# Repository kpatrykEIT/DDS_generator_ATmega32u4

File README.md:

# DDS_generator_ATmega32u4

Periodic waveform generator project based on Direct Digital Synthesis (DDS). The system utilizes an ATmega32u4 microcontroller and a TLC7524C DAC. Developed low-level firmware in C using direct register manipulation. Designed the PCB in KiCad.

<table>
  <tr>
    <td></td>
    <td></td>
  </tr>
  <tr>
    <td></td>
  <td></td>
  </tr>
</table>

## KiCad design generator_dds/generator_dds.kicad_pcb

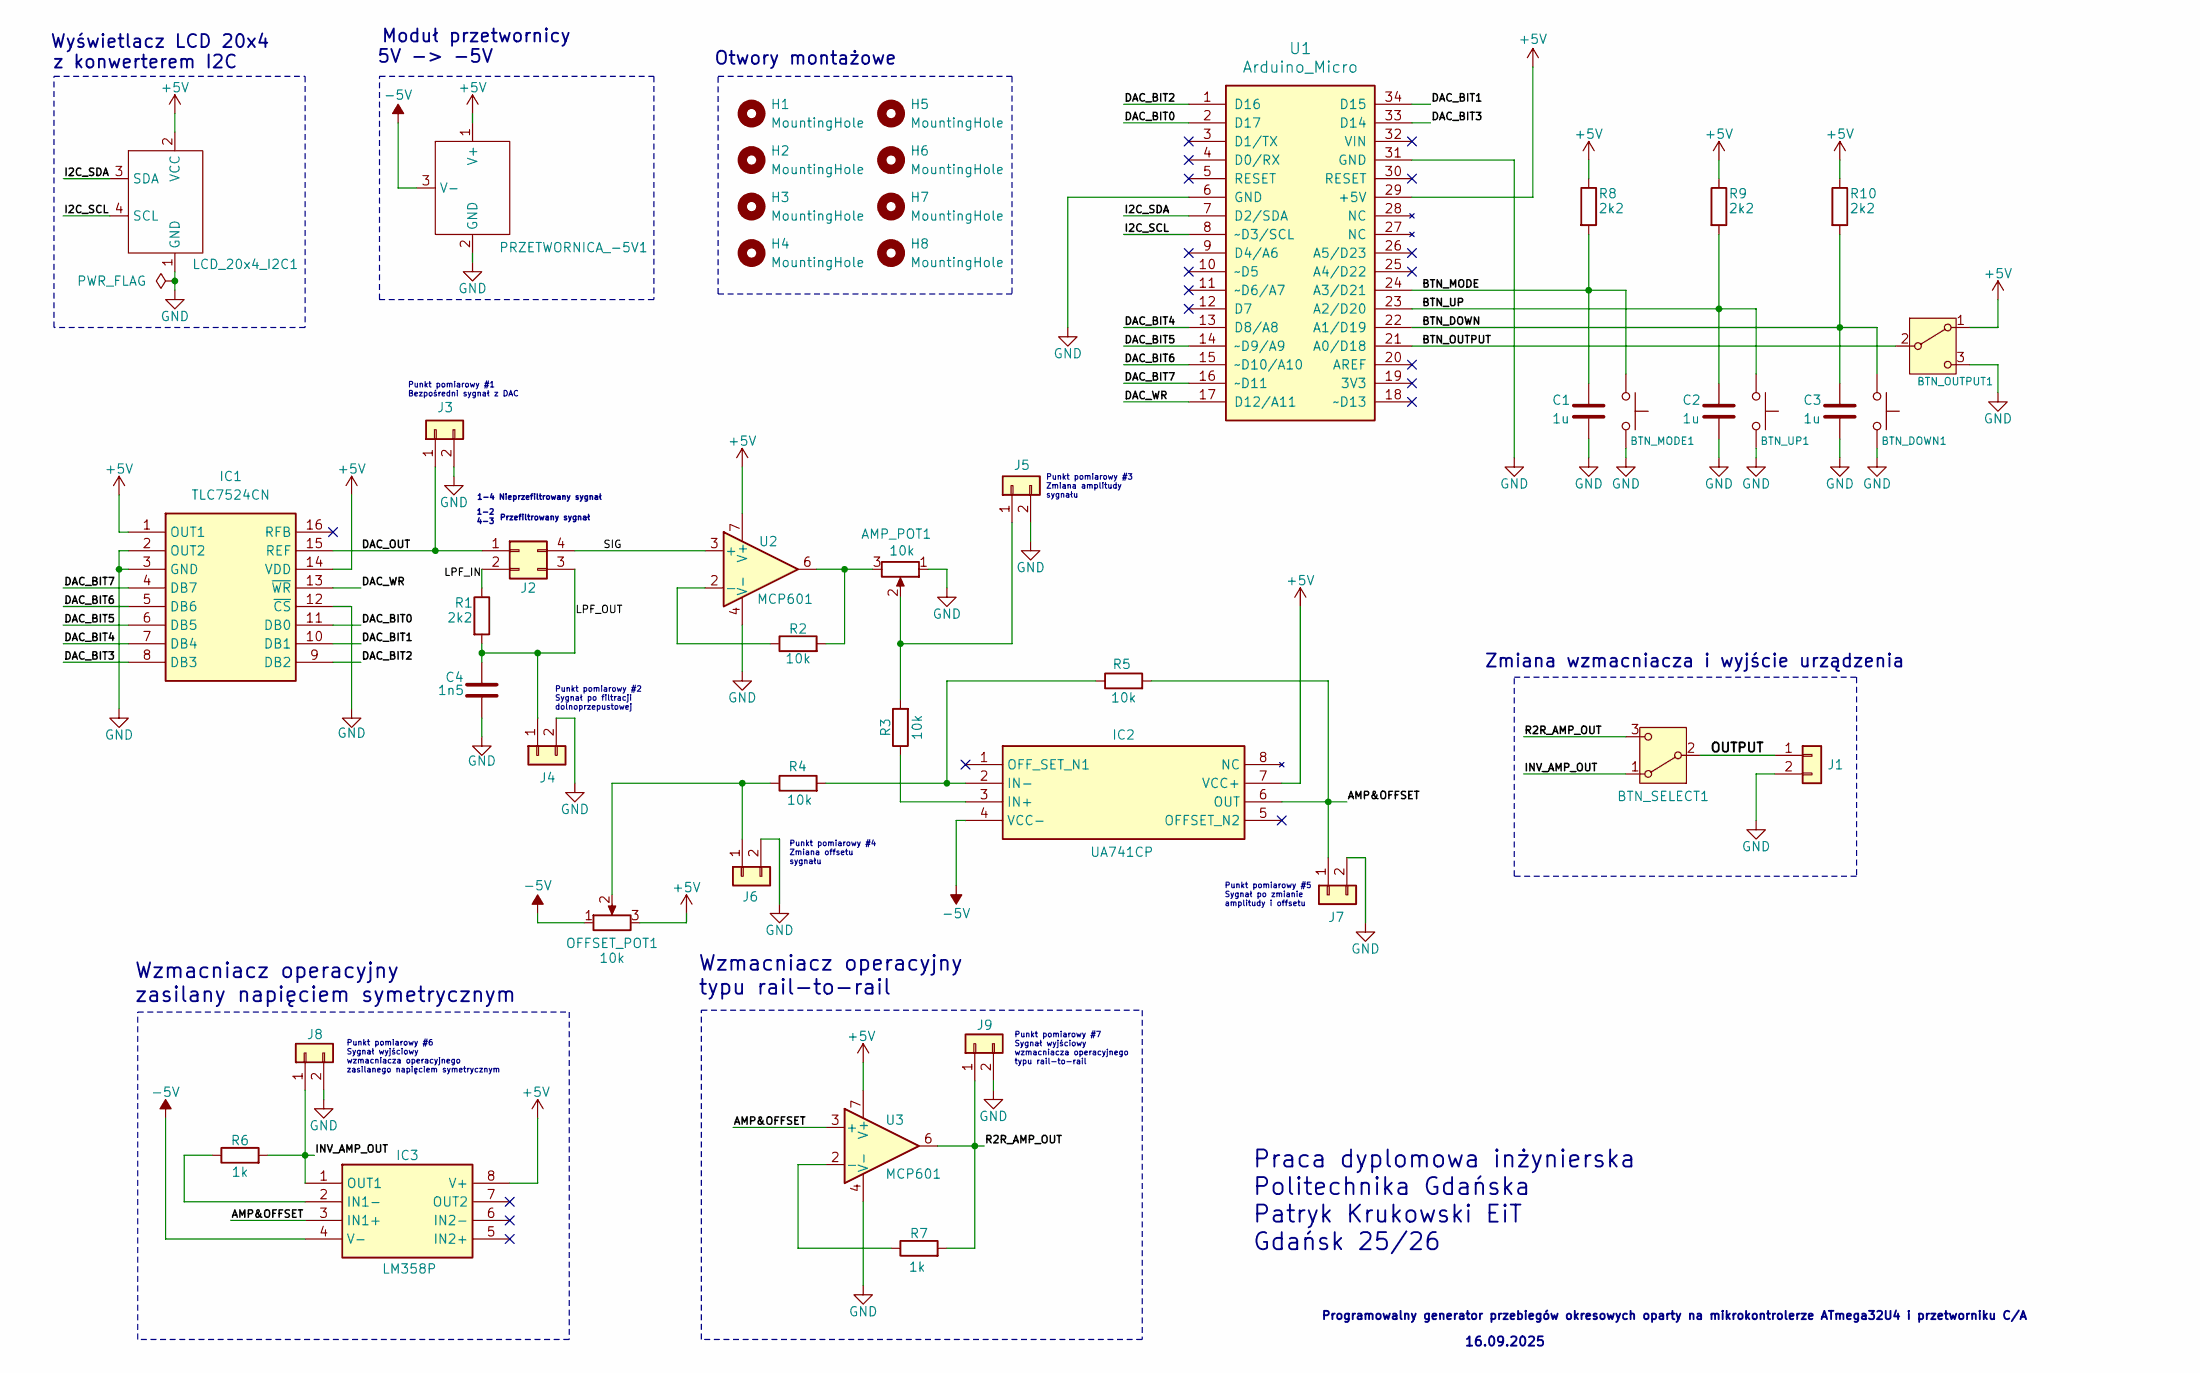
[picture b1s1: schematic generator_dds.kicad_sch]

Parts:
AMP_POT1: 10k; Potentiometer_Runtron_RM-065_Vertical
BTN_DOWN1: SW_Push; PRZYCISK_2P_5mm
BTN_MODE1: SW_Push; PRZYCISK_2P_5mm
BTN_OUTPUT1: SW_SPDT; PRZELACZNIK_SPDT_5mm
BTN_SELECT1: SW_SPDT; PRZELACZNIK_SPDT_5mm
BTN_UP1: SW_Push; PRZYCISK_2P_5mm
C1, C2, C3: 1u; C_Disc_D3.4mm_W2.1mm_P2.50mm
C4: 1n5; C_Disc_D4.3mm_W1.9mm_P5.00mm
H1, H2, H3, H4, H5, H6, H7, H8: MountingHole; MountingHole_4.3mm_M4_DIN965_Pad
IC1: TLC7524CN; DIP794W53P254L1930H508Q16N; Mouser Part Number 595-TLC7524CN
IC2: UA741CP; DIP794W53P254L959H508Q8N; Mouser Part Number 595-UA741CP
IC3: LM358P; DIP794W53P254L959H508Q8N; Mouser Part Number 595-LM358P
J1, J3, J4, J5, J6, J7, J8, J9: Conn_01x02; PinHeader_1x02_P2.54mm_Vertical
J2: Conn_02x02_Counter_Clockwise; PinHeader_2x02_P2.00mm_Vertical
LCD_20x4_I2C1: LCD_20x4_I2C_TESTfp
OFFSET_POT1: 10k; Potentiometer_Runtron_RM-065_Vertical
PRZETWORNICA_-5V1: PRZETWORNICA_5V
R1, R8, R9, R10: 2k2; R_Axial_DIN0207_L6.3mm_D2.5mm_P7.62mm_Horizontal
R2, R3, R4, R5: 10k; R_Axial_DIN0207_L6.3mm_D2.5mm_P7.62mm_Horizontal
R6, R7: 1k; R_Axial_DIN0207_L6.3mm_D2.5mm_P7.62mm_Horizontal
U1: Arduino_Micro
U2, U3: MCP601; DIP-8_W7.62mm

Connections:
+5V: BTN_OUTPUT1.1 (A), IC1.1 (OUT1), IC1.14 (VDD), IC2.7 (VCC+), IC3.8 (V+), LCD_20x4_I2C1.2 (VCC), OFFSET_POT1.3, PRZETWORNICA_-5V1.1 (V+), R8.1, R9.1, R10.1, U1.29 (+5V), U2.7 (V+), U3.7 (V+); also elsewhere on the board
-5V: IC2.4 (VCC-), IC3.4 (V-), OFFSET_POT1.1, PRZETWORNICA_-5V1.3 (V-); also elsewhere on the board
/AMP&OFFSET: IC2.6 (OUT), IC3.3 (IN1+), J7.1, R5.2, U3.3 (+)
/BTN_DOWN: BTN_DOWN1.1, C3.1, R10.2, U1.22 (A1/D19)
/BTN_MODE: BTN_MODE1.1, C1.1, R8.2, U1.24 (A3/D21)
/BTN_OUTPUT: BTN_OUTPUT1.2 (B), U1.21 (A0/D18); also elsewhere on the board
/BTN_UP: BTN_UP1.1, C2.1, R9.2, U1.23 (A2/D20)
/DAC_BIT0: IC1.11 (DB0), U1.2 (D17)
/DAC_BIT1: IC1.10 (DB1), U1.34 (D15)
/DAC_BIT2: IC1.9 (DB2), U1.1 (D16)
/DAC_BIT3: IC1.8 (DB3), U1.33 (D14)
/DAC_BIT4: IC1.7 (DB4), U1.13 (D8/A8)
/DAC_BIT5: IC1.6 (DB5), U1.14 (~D9/A9)
/DAC_BIT6: IC1.5 (DB6), U1.15 (~D10/A10)
/DAC_BIT7: IC1.4 (DB7), U1.16 (~D11)
/DAC_OUT: IC1.15 (REF), J2.1, J3.1
/DAC_WR: IC1.13 (~WR), U1.17 (D12/A11)
/I2C_SCL: LCD_20x4_I2C1.4 (SCL), U1.8 (~D3/SCL)
/I2C_SDA: LCD_20x4_I2C1.3 (SDA), U1.7 (D2/SDA)
/INV_AMP_OUT: BTN_SELECT1.1 (A), IC3.1 (OUT1), J8.1, R6.2; also elsewhere on the board
/LPF_IN: J2.2, R1.1
/LPF_OUT: C4.1, J2.3, J4.1, R1.2
/OUTPUT: BTN_SELECT1.2 (B), J1.1; also elsewhere on the board
/R2R_AMP_OUT: BTN_SELECT1.3 (C), J9.1, R7.2, U3.6; also elsewhere on the board
/SIG: J2.4, U2.3 (+)
GND: AMP_POT1.1, BTN_DOWN1.2, BTN_MODE1.2, BTN_OUTPUT1.3 (C), BTN_UP1.2, C1.2, C2.2, C3.2, C4.2, IC1.2 (OUT2), IC1.3 (GND), IC1.12 (~CS), J1.2, J3.2, J4.2, J5.2, J6.2, J7.2, J8.2, J9.2, LCD_20x4_I2C1.1 (GND), PRZETWORNICA_-5V1.2 (GND), U1.6 (GND), U1.31 (GND), U2.4 (V-), U3.4 (V-); also elsewhere on the board
unnamed 26: AMP_POT1.3, R2.2, U2.6; also elsewhere on the board
unnamed: IC2.3 (IN+), R3.1
unnamed: IC2.2 (IN-), R4.2, R5.1
unnamed: IC3.2 (IN1-), R6.1
unnamed 30: AMP_POT1.2, J5.1, R3.2; also elsewhere on the board
unnamed 31: J6.1, OFFSET_POT1.2, R4.1; also elsewhere on the board
unnamed: R2.1, U2.2 (-)
unnamed: R7.1, U3.2 (-)

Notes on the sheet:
Przefiltrowany sygnał
1-4 Nieprzefiltrowany sygnał
Wyświetlacz LCD 20x4
Otwory montażowe
Wzmacniacz operacyjny typu rail-to-rail
5V -> -5V
Punkt pomiarowy #7 Sygnał wyjściowy wzmacniacza operacyjnego typu rail-to-rail
Punkt pomiarowy #1 Bezpośredni sygnał z DAC
1-2
Punkt pomiarowy #2 Sygnał po filtracji dolnoprzepustowej
Praca dyplomowa inżynierska Politechnika Gdańska Patryk Krukowski EiT Gdańsk 25/26
16.09.2025
z konwerterem I2C
Moduł przetwornicy
Punkt pomiarowy #5 Sygnał po zmianie amplitudy i offsetu
Punkt pomiarowy #3 Zmiana amplitudy sygnału
Punkt pomiarowy #4 Zmiana offsetu sygnału
4-3
Zmiana wzmacniacza i wyjście urządzenia
Programowalny generator przebiegów okresowych oparty na mikrokontrolerze ATmega32U4 i przetworniku C/A
Punkt pomiarowy #6 Sygnał wyjściowy wzmacniacza operacyjnego zasilanego napięciem symetrycznym
Wzmacniacz operacyjny zasilany napięciem symetrycznym

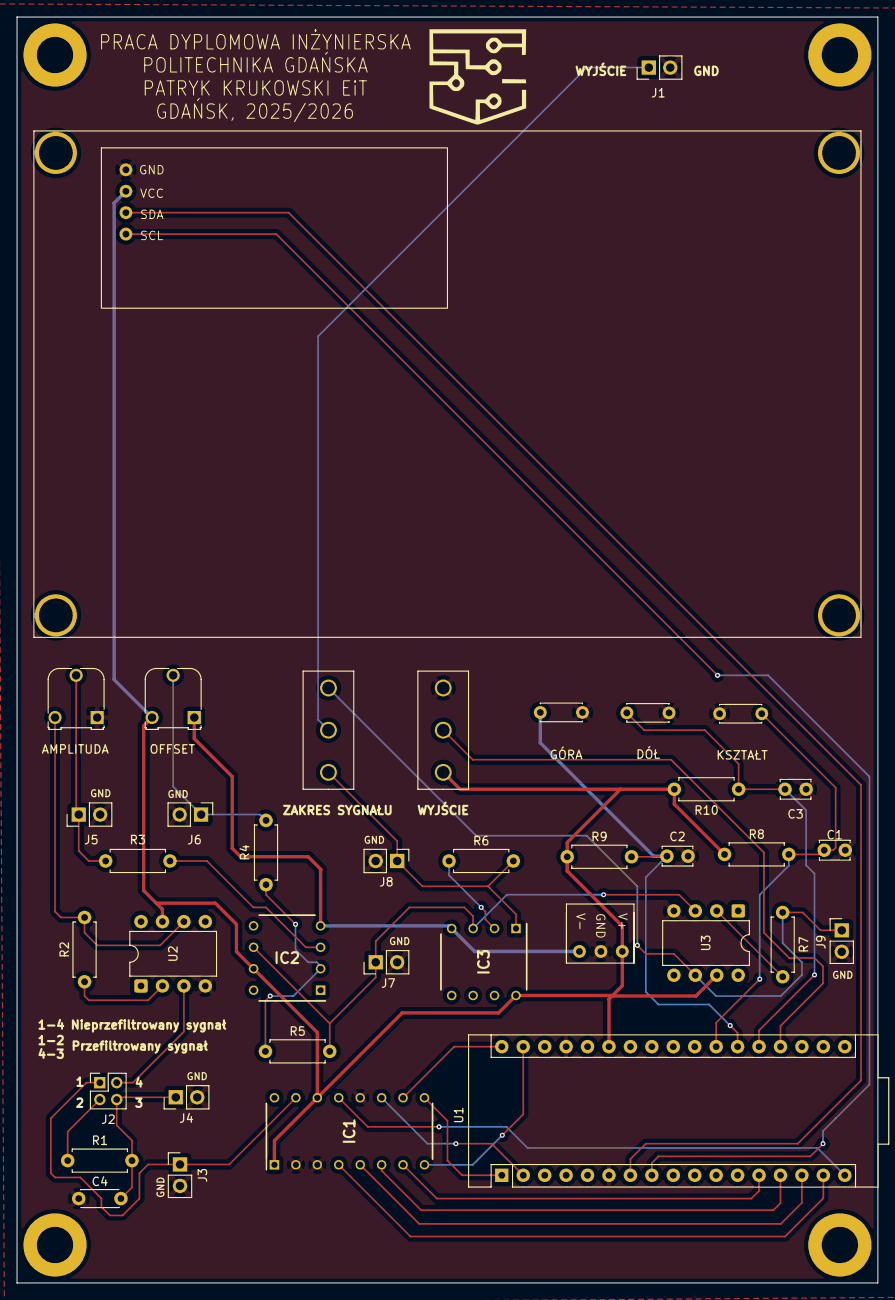
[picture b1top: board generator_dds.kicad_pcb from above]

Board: 4 copper layers, 102.0 x 150.0 mm, 46 parts (0 on the bottom side), 34 nets.

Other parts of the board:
AMPLITUDA: 10k; Potentiometer_Runtron_RM-065_Vertical
OFFSET: 10k; Potentiometer_Runtron_RM-065_Vertical
WYJŚCIE: SW_SPDT; PRZELACZNIK_SPDT_5mm
ZAKRES SYGNAŁU: SW_SPDT; PRZELACZNIK_SPDT_5mm

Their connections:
+5V: OFFSET.3, WYJŚCIE.1 (A); also elsewhere on the board
-5V: OFFSET.1; also elsewhere on the board
/BTN_OUTPUT: WYJŚCIE.2 (B); also elsewhere on the board
/INV_AMP_OUT: ZAKRES SYGNAŁU.1 (A); also elsewhere on the board
/OUTPUT: ZAKRES SYGNAŁU.2 (B); also elsewhere on the board
/R2R_AMP_OUT: ZAKRES SYGNAŁU.3 (C); also elsewhere on the board
GND: AMPLITUDA.1, WYJŚCIE.3 (C); also elsewhere on the board
unnamed 26: AMPLITUDA.3; also elsewhere on the board
unnamed 30: AMPLITUDA.2; also elsewhere on the board
unnamed 31: OFFSET.2; also elsewhere on the board

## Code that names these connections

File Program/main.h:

/*
 * File: main.h
 *
 * Created: 02.06.2025 17:09:30
 *  Author: Patryk Krukowski
 */ 


#ifndef MAIN_H_
#define MAIN_H_

// BIBLIOTEKI

#include <avr/io.h>
#include <avr/interrupt.h>
#include <util/delay.h>
#include <stdint.h>
#include <stdio.h>
#include <stdlib.h>
#include <stdbool.h>
#include <math.h>
#include "sin_wave.h"
#include "sawtooth_wave.h"
#include "square_wave.h"
#include "triangle_wave.h"
#include "i2c_master.h"
#include "liquid_crystal_i2c.h"

// PRZYCISKI

#define BTN_MODE	PF4		// zmien ksztalt przebiegu
#define BTN_UP		PF5		// zwieksz czestotliwosc
#define BTN_DOWN	PF6		// zmniejsz czestotliwosc
#define BTN_OUTPUT	PF7		// wlacz/wylacz wyjscie generatora

// PRZETWORNIK C/A


#define DAC_WR	PD6
#define DAC_DB0 PB0
#define DAC_DB1 PB1
#define DAC_DB2 PB2
#define DAC_DB3 PB3
#define DAC_DB4 PB4
#define DAC_DB5 PB5
#define DAC_DB6 PB6
#define DAC_DB7 PB7
#define DAC_OUTPUT	PORTB


// MAKRA

#define BTN_PRESSED(PIN,BIT)	(!((PIN) & (1 << (BIT))))

// FUNKCJE

inline void avr_init(void);
void display_author_info(struct LiquidCrystalDevice_t device);
void main_menu(struct LiquidCrystalDevice_t device, uint8_t mode, bool output, int32_t fout);
inline void timer1_init(void);

#endif /* MAIN_H_ */

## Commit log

2026-03-22 Pliki projektu PCB
